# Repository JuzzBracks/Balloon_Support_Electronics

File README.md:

# Balloon_Support_Electronics
 Modular designs and support materials for scientific Ballooning support electronics. The goal is to lower the time/financial costs of developing and deploying scientific balloons.

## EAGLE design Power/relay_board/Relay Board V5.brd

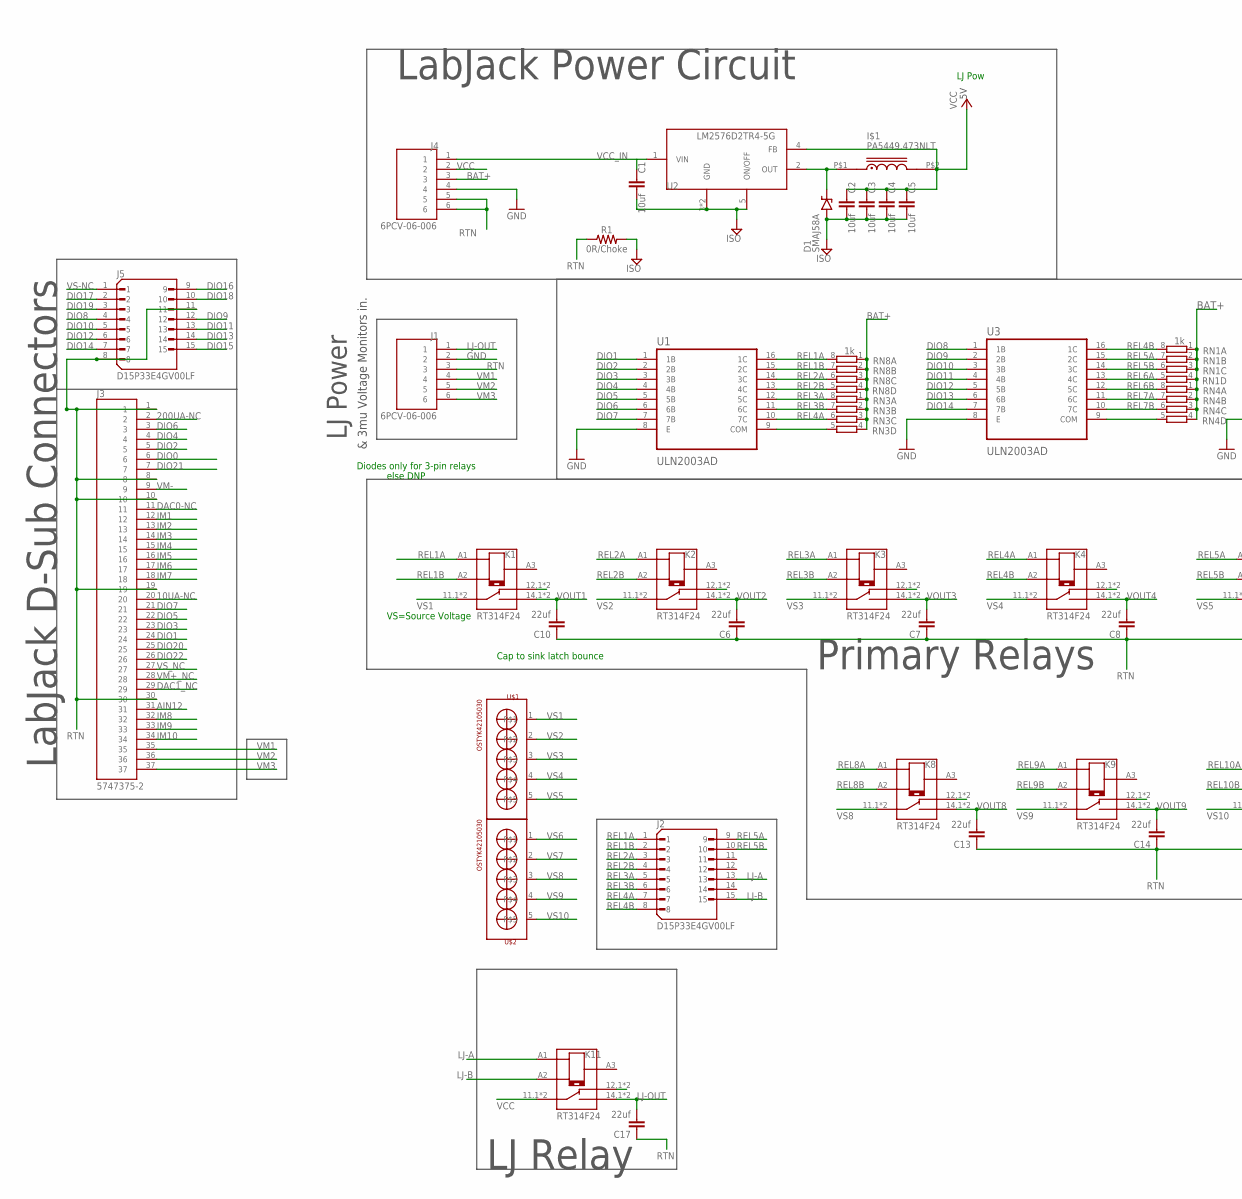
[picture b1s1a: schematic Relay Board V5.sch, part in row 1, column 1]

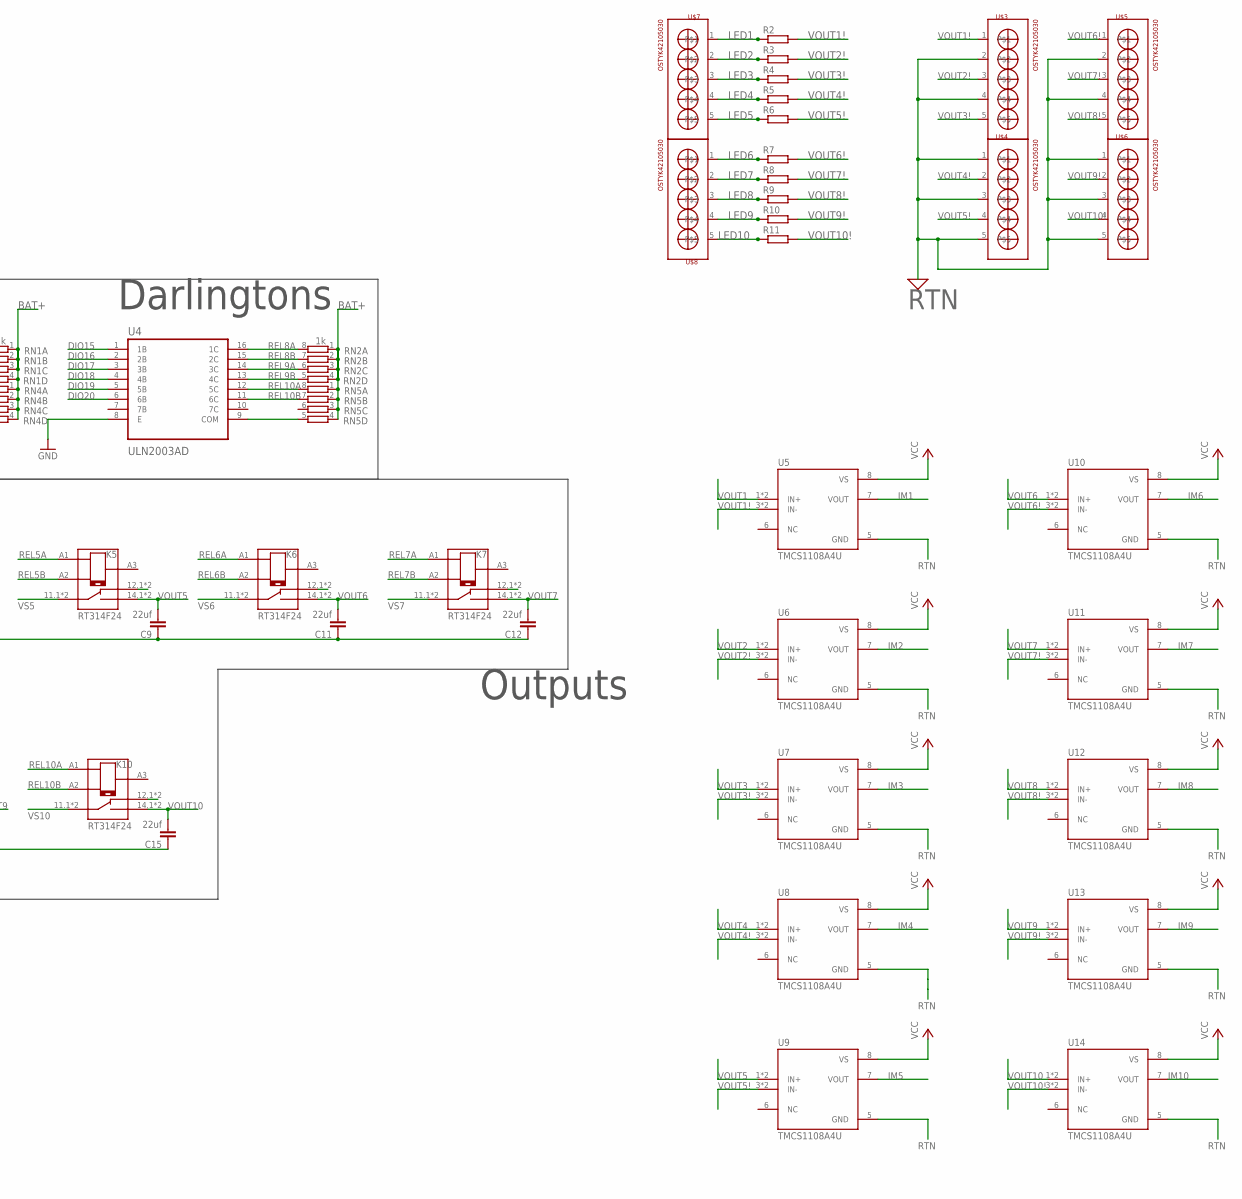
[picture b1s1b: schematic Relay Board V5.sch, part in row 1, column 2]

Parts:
C1, C2, C3, C4, C5: 10uf; 0805
C6, C7, C8, C9, C10, C11, C12, C13, C14, C15, C17: 22uf; 0603
D1: SMAJ58A; SMA
I$1: PA5449.473NLT; IND_TYS4020470M-10
J1, J4: 6PCV-06-006; TE_9-1437652-5
J2, J5: D15P33E4GV00LF; AMPHENOL_D15P33E4GV00LF
J3: 5747375-2; TE_5747375-2
K1, K2, K3, K4, K5, K6, K7, K8, K9, K10, K11: RT314F24; TE_8-1393239-8
R1: 0R/Choke; 0603
R2, R3, R4, R5, R6, R7, R8, R9, R10, R11: R-EU_0204/7; 0204/7
RN1, RN2, RN3, RN4, RN5, RN8: 1k; CAY16
U1, U3, U4: ULN2003AD; SOIC127P600X175-16N
U2: LM2576D2TR4-5G; D2PAK-5
U5, U6, U7, U8, U9, U10, U11, U12, U13, U14: TMCS1108A4U; SOIC127P599X175-8N
U$1, U$2, U$3, U$4, U$5, U$6, U$7, U$8: OSTYK42105030

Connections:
10UA-NC: J3.20
200UA-NC: J3.2
AGND: C1.2, C2.2, C3.2, C4.2, C5.2, D1.A, R1.2, U2.3 (GND), U2.5 (ON/OFF), U2.6 (GND)
AIN12: J3.31
BAT+: J4.3, RN1.1, RN1.2 (1), RN1.3 (1), RN1.4 (1), RN2.1, RN2.2 (1), RN2.3 (1), RN2.4 (1), RN3.1, RN3.2 (1), RN3.3 (1), RN3.4 (1), RN4.1, RN4.2 (1), RN4.3 (1), RN4.4 (1), RN5.1, RN5.2 (1), RN5.3 (1), RN5.4 (1), RN8.1, RN8.2 (1), RN8.3 (1), RN8.4 (1)
DAC0-NC: J3.11
DAC1_NC: J3.29
DIO0: J3.6
DIO1: J3.24, U1.1 (1B)
DIO2: J3.5, U1.2 (2B)
DIO3: J3.23, U1.3 (3B)
DIO4: J3.4, U1.4 (4B)
DIO5: J3.22, U1.5 (5B)
DIO6: J3.3, U1.6 (6B)
DIO7: J3.21, U1.7 (7B)
DIO8: J5.4, U3.1 (1B)
DIO9: J5.12, U3.2 (2B)
DIO10: J5.5, U3.3 (3B)
DIO11: J5.13, U3.4 (4B)
DIO12: J5.6, U3.5 (5B)
DIO13: J5.14, U3.6 (6B)
DIO14: J5.7, U3.7 (7B)
DIO15: J5.15, U4.1 (1B)
DIO16: J5.9, U4.2 (2B)
DIO17: J5.2, U4.3 (3B)
DIO18: J5.10, U4.4 (4B)
DIO19: J5.3, U4.5 (5B)
DIO20: J3.25, U4.6 (6B)
DIO21: J3.7
DIO22: J3.26
GND: J1.2, J4.4, U1.8 (E), U3.8 (E), U4.8 (E)
IM1: J3.12, U5.7 (VOUT)
IM2: J3.13, U6.7 (VOUT)
IM3: J3.14, U7.7 (VOUT)
IM4: J3.15, U8.7 (VOUT)
IM5: J3.16, U9.7 (VOUT)
IM6: J3.17, U10.7 (VOUT)
IM7: J3.18, U11.7 (VOUT)
IM8: J3.32, U12.7 (VOUT)
IM9: J3.33, U13.7 (VOUT)
IM10: J3.34, U14.7 (VOUT)
LED1: R2.1, U$7.1
LED2: R3.1, U$7.2
LED3: R4.1, U$7.3
LED4: R5.1, U$7.4
LED5: R6.1, U$7.5
LED6: R7.1, U$8.1
LED7: R8.1, U$8.2
LED8: R9.1, U$8.3
LED9: R10.1, U$8.4
LED10: R11.1, U$8.5
LJ-A: J2.13, K11.A1
LJ-B: J2.15, K11.A2
LJ-OUT: C17.2, J1.1, K11.14.1 (14), K11.14.2 (14)
unnamed: K1.12.1 (12), K1.12.2 (12)
unnamed: RN3.5 (2), U1.9 (COM)
unnamed: K2.12.1 (12), K2.12.2 (12)
unnamed: K3.12.1 (12), K3.12.2 (12)
unnamed: D1.C, I$1.P$1 (1), U2.2 (OUT)
unnamed: K4.12.1 (12), K4.12.2 (12)
unnamed: K5.12.1 (12), K5.12.2 (12)
unnamed: K6.12.1 (12), K6.12.2 (12)
unnamed: K7.12.1 (12), K7.12.2 (12)
unnamed: RN4.5 (2), U3.9 (COM)
unnamed: K8.12.1 (12), K8.12.2 (12)
unnamed: K9.12.1 (12), K9.12.2 (12)
unnamed: K10.12.1 (12), K10.12.2 (12)
unnamed: RN5.5 (2), U4.9 (COM)
unnamed: K11.12.1 (12), K11.12.2 (12)
REL1A: J2.1, K1.A1, RN8.8 (2), U1.16 (1C)
REL1B: J2.2, K1.A2, RN8.7 (2), U1.15 (2C)
REL2A: J2.3, K2.A1, RN8.6 (2), U1.14 (3C)
REL2B: J2.4, K2.A2, RN8.5 (2), U1.13 (4C)
REL3A: J2.5, K3.A1, RN3.8 (2), U1.12 (5C)
REL3B: J2.6, K3.A2, RN3.7 (2), U1.11 (6C)
REL4A: J2.7, K4.A1, RN3.6 (2), U1.10 (7C)
REL4B: J2.8, K4.A2, RN1.8 (2), U3.16 (1C)
REL5A: J2.9, K5.A1, RN1.7 (2), U3.15 (2C)
REL5B: J2.10, K5.A2, RN1.6 (2), U3.14 (3C)
REL6A: K6.A1, RN1.5 (2), U3.13 (4C)
REL6B: K6.A2, RN4.8 (2), U3.12 (5C)
REL7A: K7.A1, RN4.7 (2), U3.11 (6C)
REL7B: K7.A2, RN4.6 (2), U3.10 (7C)
REL8A: K8.A1, RN2.8 (2), U4.16 (1C)
REL8B: K8.A2, RN2.7 (2), U4.15 (2C)
REL9A: K9.A1, RN2.6 (2), U4.14 (3C)
REL9B: K9.A2, RN2.5 (2), U4.13 (4C)
REL10A: K10.A1, RN5.8 (2), U4.12 (5C)
REL10B: K10.A2, RN5.7 (2), U4.11 (6C)
RTN: C6.1, C7.1, C8.1, C9.1, C10.1, C11.1, C12.1, C13.1, C14.1, C15.1, C17.1, J1.3, J3.1, J3.8, J3.10, J3.19, J3.30, J4.5, J4.6, J5.8, J5.11, R1.1, U5.5 (GND), U6.5 (GND), U7.5 (GND), U8.5 (GND), U9.5 (GND), U10.5 (GND), U11.5 (GND), U12.5 (GND), U13.5 (GND), U14.5 (GND), U$3.2, U$3.4, U$4.1, U$4.3, U$4.5, U$5.2, U$5.4, U$6.1, U$6.3, U$6.5
VCC: C2.1, C3.1, C4.1, C5.1, I$1.P$2 (2), J4.2, K11.11.1 (11), K11.11.2 (11), U2.4 (FB), U5.8 (VS), U6.8 (VS), U7.8 (VS), U8.8 (VS), U9.8 (VS), U10.8 (VS), U11.8 (VS), U12.8 (VS), U13.8 (VS), U14.8 (VS)
VCC_IN: J4.1, U2.1 (VIN)
VM1: J1.4, J3.35
VM2: J1.5, J3.36
VM3: J1.6, J3.37
VM+_NC: J3.28
VM-: J3.9
VOUT1: C10.2, K1.14.1 (14), K1.14.2 (14), U5.1 (IN+), U5.2 (IN+)
VOUT1!: R2.2, U5.3 (IN-), U5.4 (IN-), U$3.1
VOUT2: C6.2, K2.14.1 (14), K2.14.2 (14), U6.1 (IN+), U6.2 (IN+)
VOUT2!: R3.2, U6.3 (IN-), U6.4 (IN-), U$3.3
VOUT3: C7.2, K3.14.1 (14), K3.14.2 (14), U7.1 (IN+), U7.2 (IN+)
VOUT3!: R4.2, U7.3 (IN-), U7.4 (IN-), U$3.5
VOUT4: C8.2, K4.14.1 (14), K4.14.2 (14), U8.1 (IN+), U8.2 (IN+)
VOUT4!: R5.2, U8.3 (IN-), U8.4 (IN-), U$4.2
VOUT5: C9.2, K5.14.1 (14), K5.14.2 (14), U9.1 (IN+), U9.2 (IN+)
VOUT5!: R6.2, U9.3 (IN-), U9.4 (IN-), U$4.4
VOUT6: C11.2, K6.14.1 (14), K6.14.2 (14), U10.1 (IN+), U10.2 (IN+)
VOUT6!: R7.2, U10.3 (IN-), U10.4 (IN-), U$5.1
VOUT7: C12.2, K7.14.1 (14), K7.14.2 (14), U11.1 (IN+), U11.2 (IN+)
VOUT7!: R8.2, U11.3 (IN-), U11.4 (IN-), U$5.3
VOUT8: C13.2, K8.14.1 (14), K8.14.2 (14), U12.1 (IN+), U12.2 (IN+)
VOUT8!: R9.2, U12.3 (IN-), U12.4 (IN-), U$5.5
VOUT9: C14.2, K9.14.1 (14), K9.14.2 (14), U13.1 (IN+), U13.2 (IN+)
VOUT9!: R10.2, U13.3 (IN-), U13.4 (IN-), U$6.2
VOUT10: C15.2, K10.14.1 (14), K10.14.2 (14), U14.1 (IN+), U14.2 (IN+)
VOUT10!: R11.2, U14.3 (IN-), U14.4 (IN-), U$6.4
VS1: K1.11.1 (11), K1.11.2 (11), U$1.1
VS2: K2.11.1 (11), K2.11.2 (11), U$1.2
VS3: K3.11.1 (11), K3.11.2 (11), U$1.3
VS4: K4.11.1 (11), K4.11.2 (11), U$1.4
VS5: K5.11.1 (11), K5.11.2 (11), U$1.5
VS6: K6.11.1 (11), K6.11.2 (11), U$2.1
VS7: K7.11.1 (11), K7.11.2 (11), U$2.2
VS8: K8.11.1 (11), K8.11.2 (11), U$2.3
VS9: K9.11.1 (11), K9.11.2 (11), U$2.4
VS10: K10.11.1 (11), K10.11.2 (11), U$2.5
VS-NC: J5.1
VS_NC: J3.27

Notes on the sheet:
VS=Source Voltage
Diodes only for 3-pin relays
else DNP
Cap to sink latch bounce
LJ Pow
LabJack Power Circuit
Darlingtons
Primary Relays
LJ Relay
Outputs
LabJack D-Sub Connectors
LJ Power
& 3mu Voltage Monitors in.

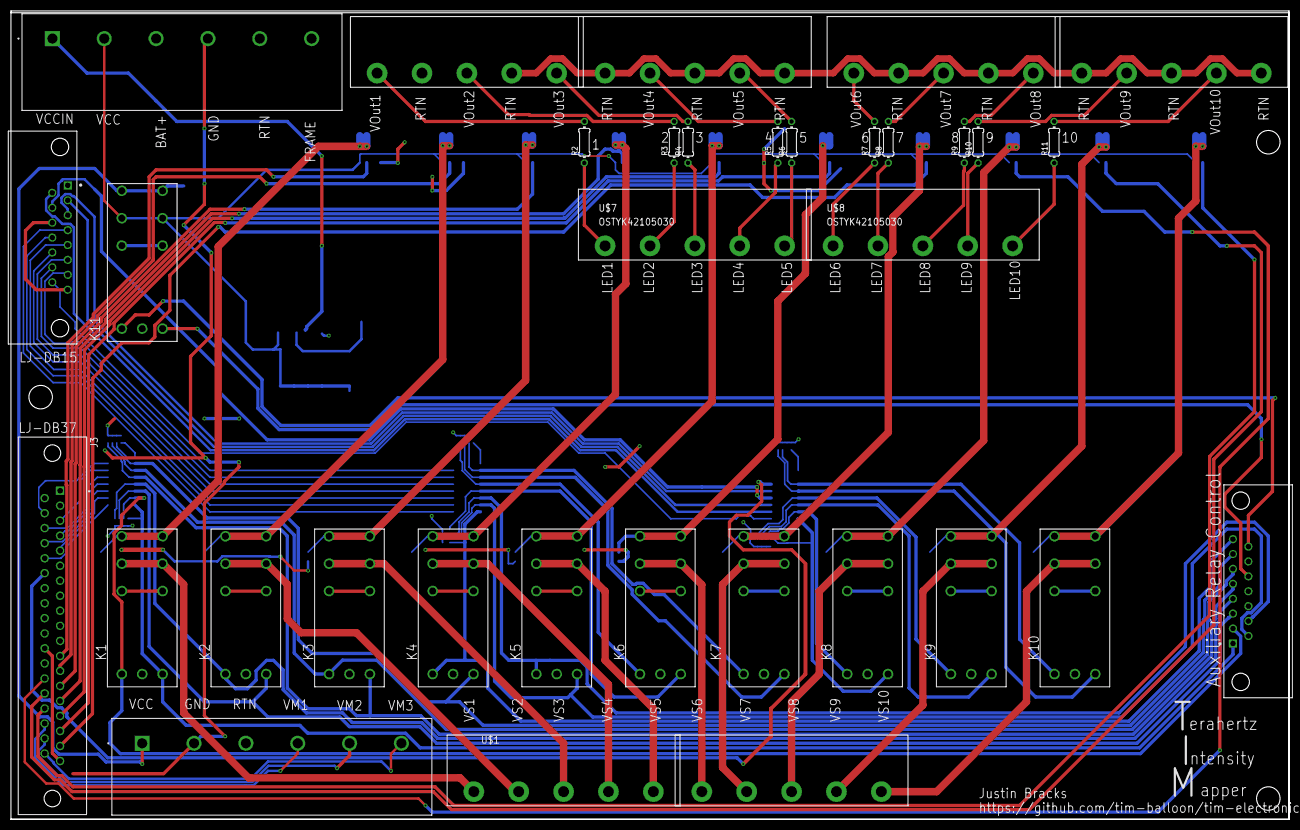
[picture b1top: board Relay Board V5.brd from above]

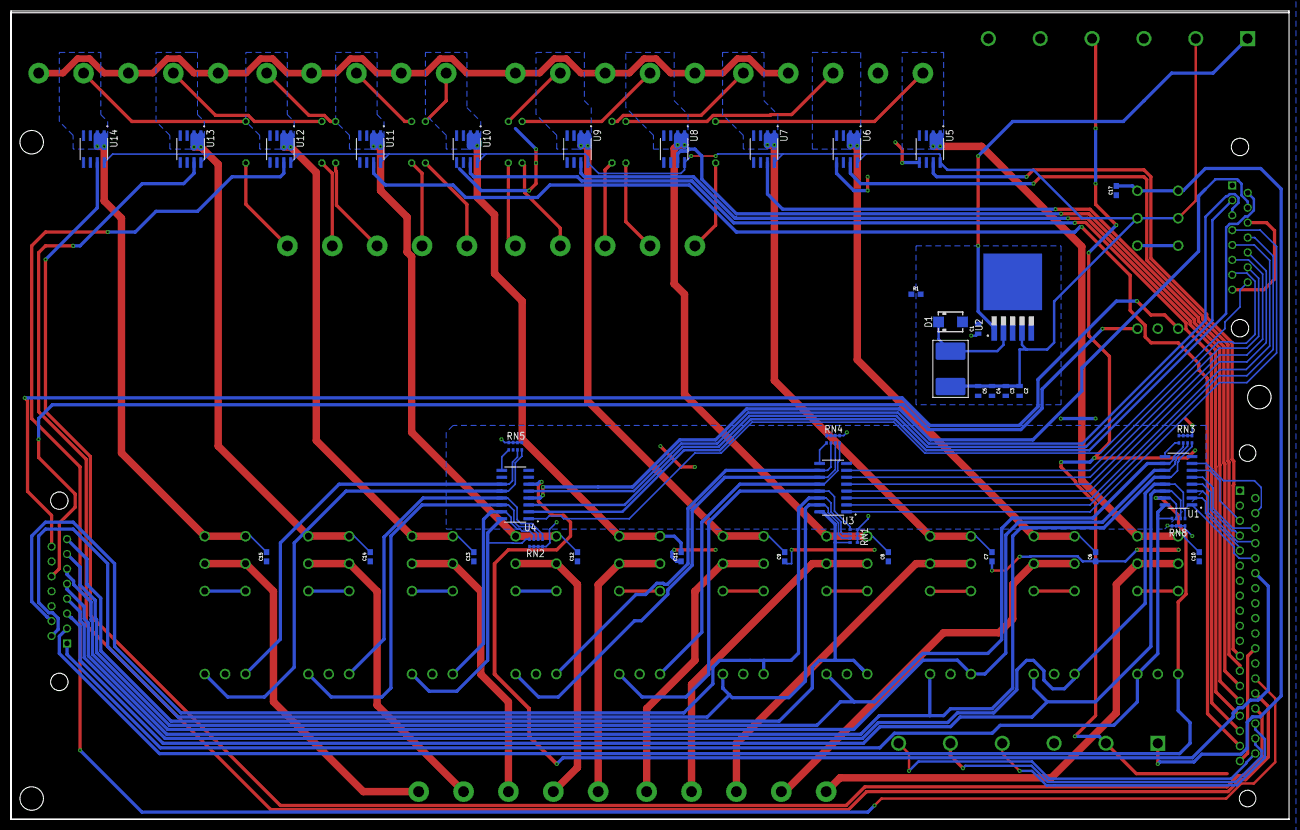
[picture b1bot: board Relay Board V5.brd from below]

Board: 2 copper layers, 234.9 x 148.6 mm, 73 parts (39 on the bottom side), 117 nets.

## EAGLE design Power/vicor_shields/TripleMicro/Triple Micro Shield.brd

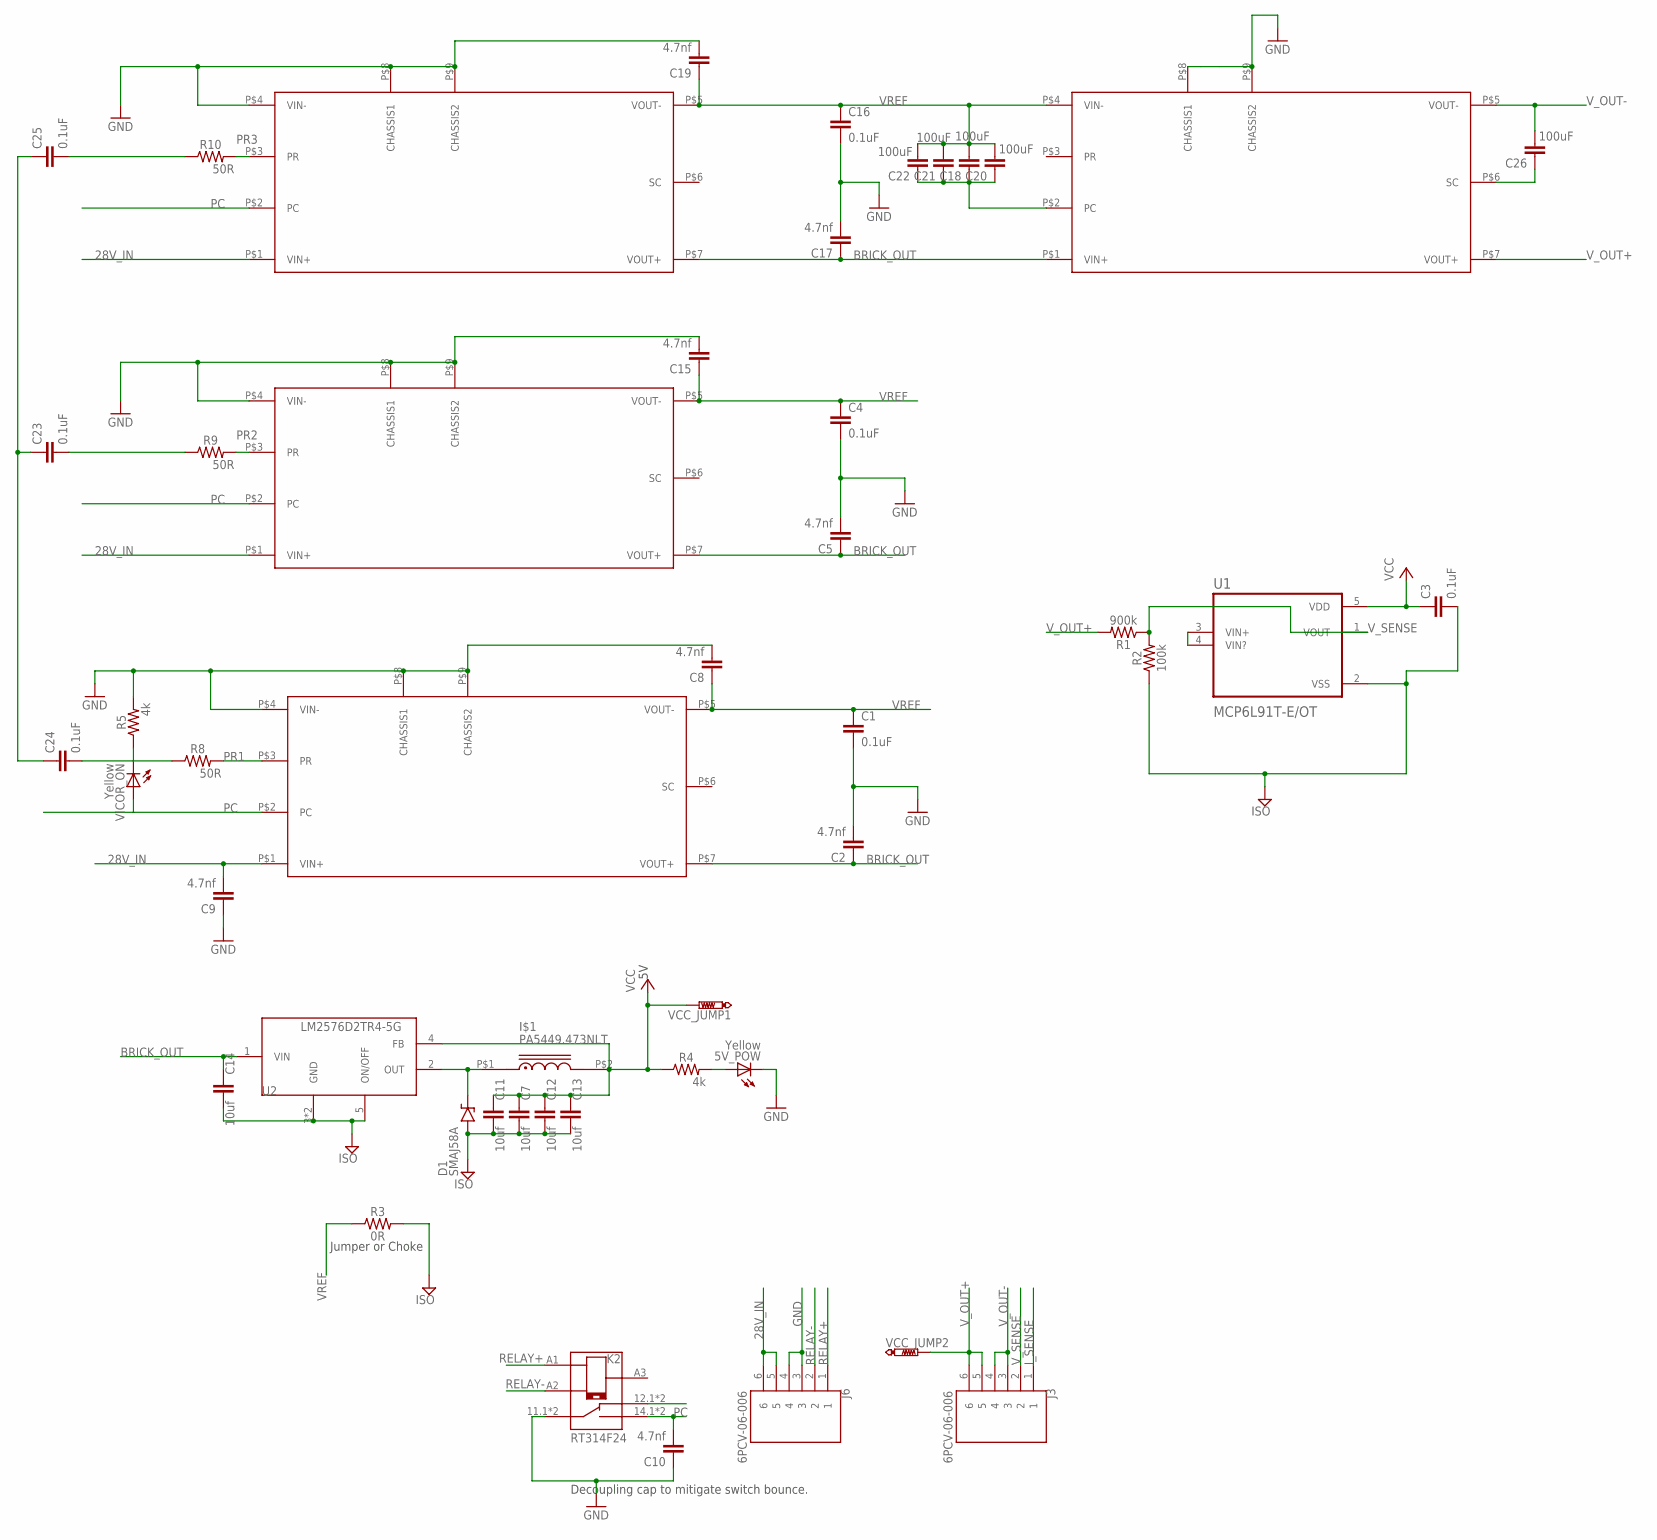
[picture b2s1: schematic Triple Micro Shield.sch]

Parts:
5V_POW: Yellow; CHIPLED_0805
C1, C3, C4, C16, C23, C24, C25: 0.1uF; 0603
C2, C5, C8, C9, C10, C15, C17, C19: 4.7nf; 0603
C7, C11, C12, C13, C14: 10uf; 0805
C18, C20, C21, C22, C26: 100uF; 0603
D1: SMAJ58A; SMA
I$1: PA5449.473NLT; IND_TYS4020470M-10
J3, J6: 6PCV-06-006; TE_9-1437652-5
K2: RT314F24; TE_8-1393239-8
R1: 900k; 0603
R2: 100k; 0603
R3: 0R; 0603
R4, R5: 4k; 0603
R8, R9, R10: 50R; 0603
U1: MCP6L91T-E/OT; SOT95P270X145-5N
U2: LM2576D2TR4-5G; D2PAK-5
U$2, U$3, U$4, U$5: VICOR_MINI_BRICK_VICORMINIBRICK; VICOR_MINI_BRICK_MINIBRICK
VCC_JUMP1, VCC_JUMP2: PTR1PAD1-13; P1-13
VICOR_ON: Yellow; CHIPLED_0805

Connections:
28V_IN: C9.2, J6.5, J6.6, U$2.P$1 (VIN+), U$3.P$1 (VIN+), U$4.P$1 (VIN+)
AGND: C3.2, C7.2, C11.2, C12.2, C13.2, C14.2, D1.A, R2.1, R3.2, U1.2 (VSS), U2.3 (GND), U2.5 (ON/OFF), U2.6 (GND)
BRICK_OUT: C2.1, C5.1, C14.1, C17.1, U2.1 (VIN), U$2.P$7 (VOUT+), U$3.P$7 (VOUT+), U$4.P$7 (VOUT+), U$5.P$1 (VIN+)
GND: 5V_POW.C, C1.2, C2.2, C4.2, C5.2, C8.2, C9.1, C10.1, C15.2, C16.2, C17.2, C19.2, J6.3, J6.4, K2.11.1 (11), K2.11.2 (11), R5.2, U$2.P$4 (VIN-), U$2.P$8 (CHASSIS1), U$2.P$9 (CHASSIS2), U$3.P$4 (VIN-), U$3.P$8 (CHASSIS1), U$3.P$9 (CHASSIS2), U$4.P$4 (VIN-), U$4.P$8 (CHASSIS1), U$4.P$9 (CHASSIS2), U$5.P$8 (CHASSIS1), U$5.P$9 (CHASSIS2)
IN+: R1.1, R2.2, U1.1 (VOUT)
I_SENSE: J3.1
unnamed: K2.12.1 (12), K2.12.2 (12)
unnamed: 5V_POW.A, R4.2
unnamed: R5.1, VICOR_ON.C
unnamed: C18.1, C20.1, C21.1, C22.1, U$5.P$2 (PC)
unnamed: D1.C, I$1.P$1 (1), U2.2 (OUT)
unnamed: C23.2, R9.1
unnamed: C23.1, C24.1, C25.1
unnamed: C24.2, R8.1
unnamed: C25.2, R10.1
unnamed: C26.1, U$5.P$6 (SC)
PC: C10.2, K2.14.1 (14), K2.14.2 (14), U$2.P$2 (PC), U$3.P$2 (PC), U$4.P$2 (PC), VICOR_ON.A
PR1: R8.2, U$2.P$3 (PR)
PR2: R9.2, U$3.P$3 (PR)
PR3: R10.2, U$4.P$3 (PR)
RELAY+: J6.1, K2.A1
RELAY-: J6.2, K2.A2
VCC: C3.1, C7.1, C11.1, C12.1, C13.1, I$1.P$2 (2), R4.1, U1.5 (VDD), U2.4 (FB), VCC_JUMP1.TP
VREF: C1.1, C4.1, C8.1, C15.1, C16.1, C18.2, C19.1, C20.2, C21.2, C22.2, R3.1, U$2.P$5 (VOUT-), U$3.P$5 (VOUT-), U$4.P$5 (VOUT-), U$5.P$4 (VIN-)
V_OUT+: J3.5, J3.6, R1.2, U$5.P$7 (VOUT+), VCC_JUMP2.TP
V_OUT-: C26.2, J3.3, J3.4, U$5.P$5 (VOUT-)
V_SENSE: J3.2, U1.3 (VIN+), U1.4 (VIN?)

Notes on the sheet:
Decoupling cap to mitigate switch bounce.
Jumper or Choke

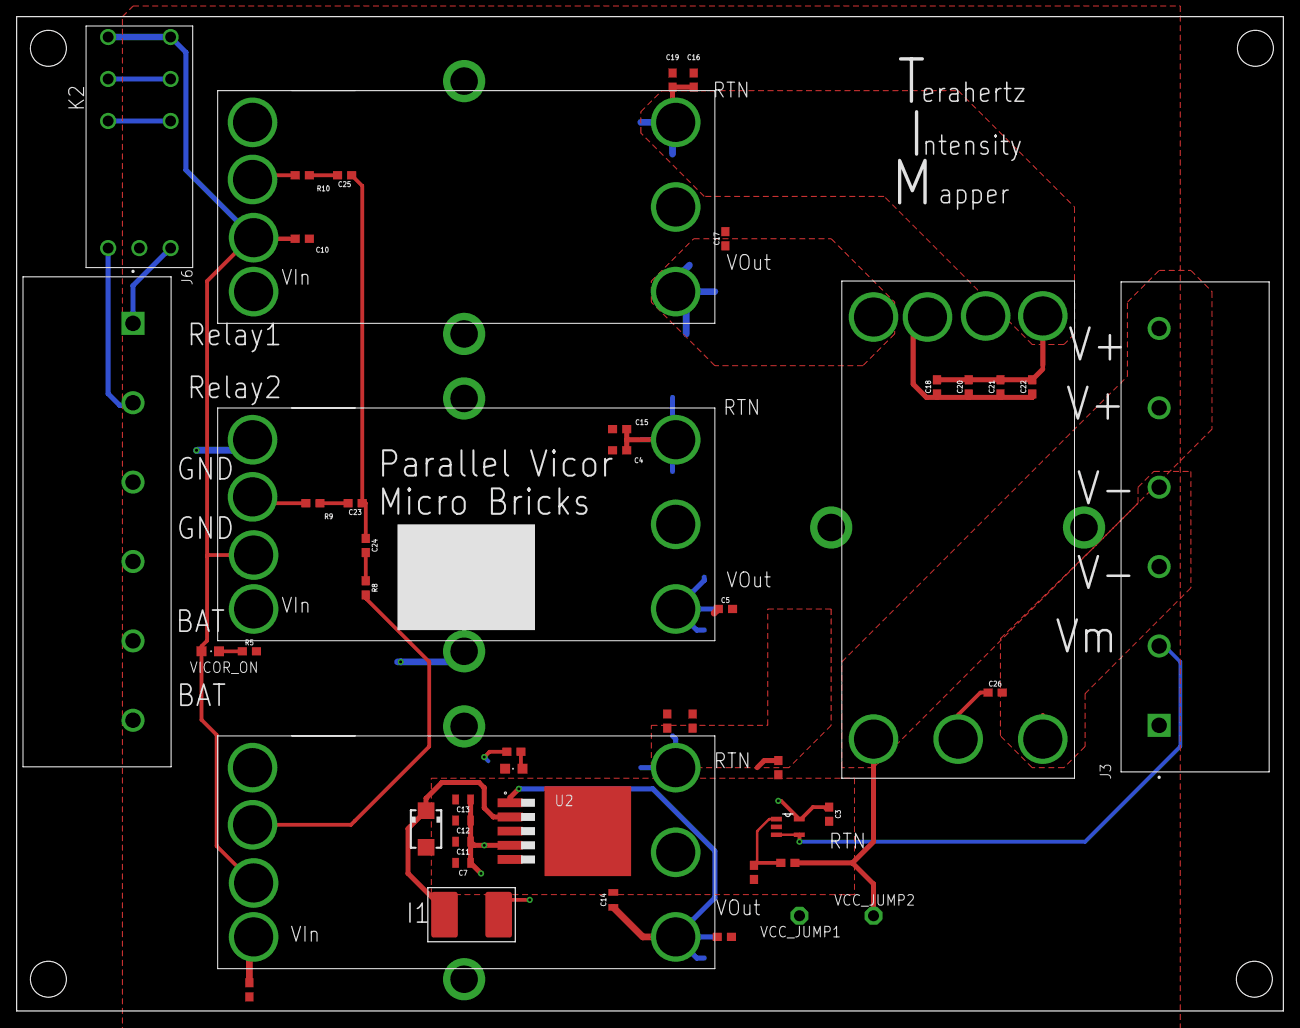
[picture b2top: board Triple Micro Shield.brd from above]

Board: 2 copper layers, 152.1 x 119.4 mm, 48 parts (0 on the bottom side), 26 nets.

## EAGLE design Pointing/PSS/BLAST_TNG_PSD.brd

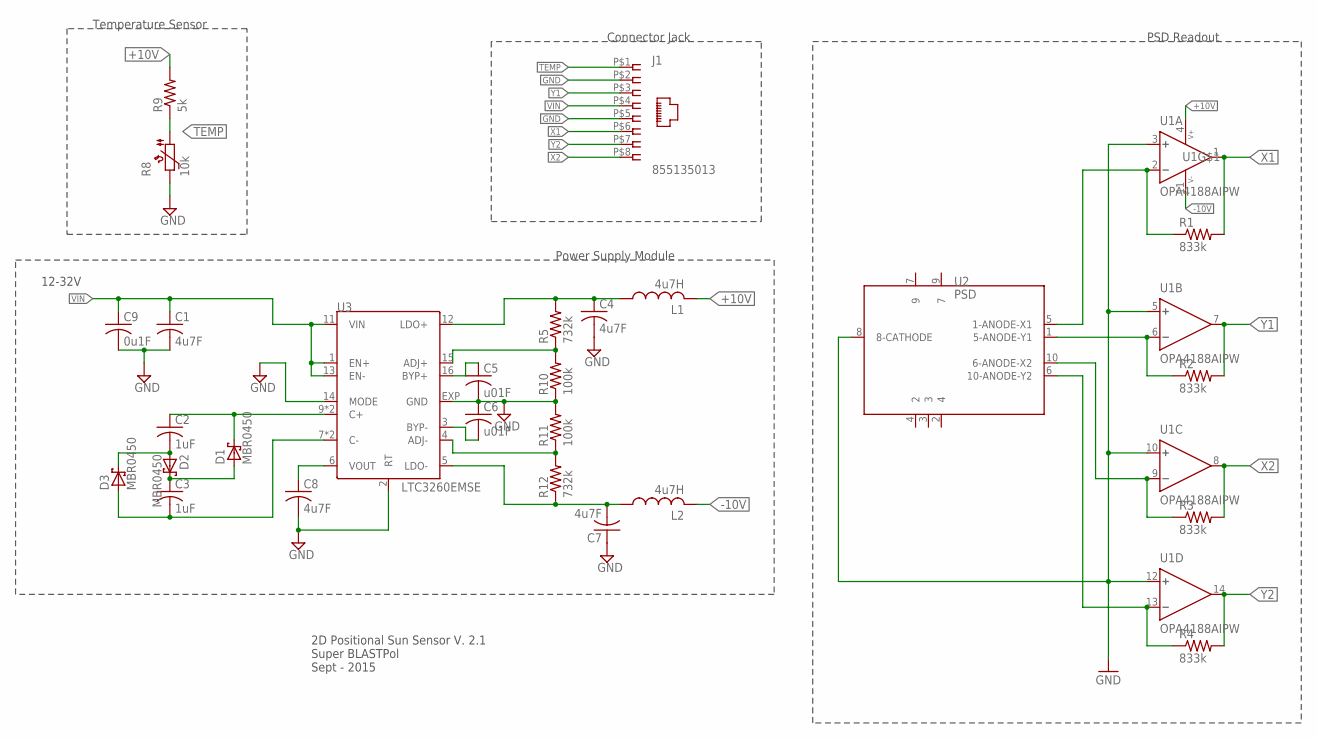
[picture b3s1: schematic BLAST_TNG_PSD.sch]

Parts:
C1, C4, C7, C8: 4u7F; C1210; MPN CL31A475KOHNNNE
C2, C3: 1uF; C1206
C5, C6: u01F; C0805
C9: 0u1F; C0805
D1, D2, D3: MBR0450; SOD123
J1: 855135013; MPN 85513-5013
L1, L2: 4u7H; L2012C
R1, R2, R3, R4: 833k; M0805
R5, R12: 732k; R0805
R8: 10k; L3216C; MPN KPTL-3216CGCK
R9: 5k; R0805
R10, R11: 100k; R0805
U1: OPA4188AIPW; TSSOP14
U2: PSD; PSD-S5991
U3: LTC3260EMSE; MSOP16

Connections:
+10V: L1.2, R9.2, U1.4 (V+)
-10V: L2.2, U1.11 (V-)
D1X1: R1.1, U1.2 (-), U2.5 (1-ANODE-X1)
D1X2: R3.1, U1.9 (-), U2.10 (6-ANODE-X2)
D1Y1: R2.1, U1.6 (-), U2.1 (5-ANODE-Y1)
D1Y2: R4.1, U1.13 (-), U2.6 (10-ANODE-Y2)
FLY+: C2.1, D1.C, U3.9 (C+), U3.10 (C+)
FLY-: C3.2, D3.A, U3.7 (C-), U3.8 (C-)
GND: C1.2, C4.2, C5.2, C6.1, C7.1, C8.2, C9.2, J1.P$2 (2), J1.P$5 (5), R8.2, R10.1, R11.2, U1.3 (+), U1.5 (+), U1.10 (+), U1.12 (+), U2.8 (8-CATHODE), U3.2 (RT), U3.14 (MODE), U3.EXP (GND)
LDO+: C4.1, L1.1, R5.2, U3.12 (LDO+)
LDO-: C7.2, L2.1, R12.1, U3.5 (LDO-)
unnamed: C8.1, U3.6 (VOUT)
unnamed: C3.1, D1.A, D2.C
unnamed: C2.2, D2.A, D3.C
unnamed: C6.2, U3.3 (BYP-)
unnamed: C5.1, U3.16 (BYP+)
unnamed: R5.1, R10.2, U3.15 (ADJ+)
unnamed: R11.1, R12.2, U3.4 (ADJ-)
TEMP: J1.P$1 (1), R8.1, R9.1
VIN: C1.1, C9.1, J1.P$4 (4), U3.1 (EN+), U3.11 (VIN), U3.13 (EN-)
X1: J1.P$6 (6), R1.2, U1.1 (OUT)
X2: J1.P$8 (8), R3.2, U1.8 (OUT)
Y1: J1.P$3 (3), R2.2, U1.7 (OUT)
Y2: J1.P$7 (7), R4.2, U1.14 (OUT)

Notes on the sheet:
Power Supply Module
12-32V
Connector Jack
Temperature Sensor
PSD Readout
2D Positional Sun Sensor V. 2.1 Super BLASTPol Sept - 2015

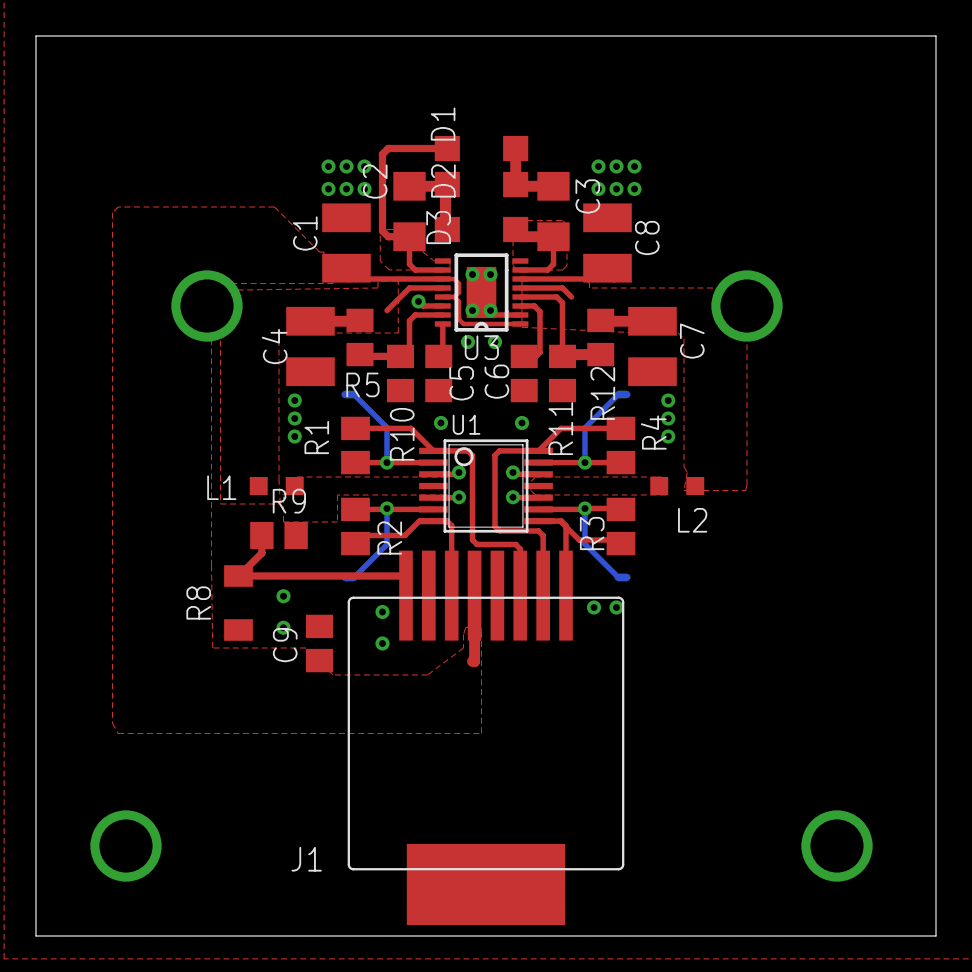
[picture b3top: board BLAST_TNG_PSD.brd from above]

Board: 2 copper layers, 50.0 x 50.0 mm, 28 parts (1 on the bottom side), 24 nets.

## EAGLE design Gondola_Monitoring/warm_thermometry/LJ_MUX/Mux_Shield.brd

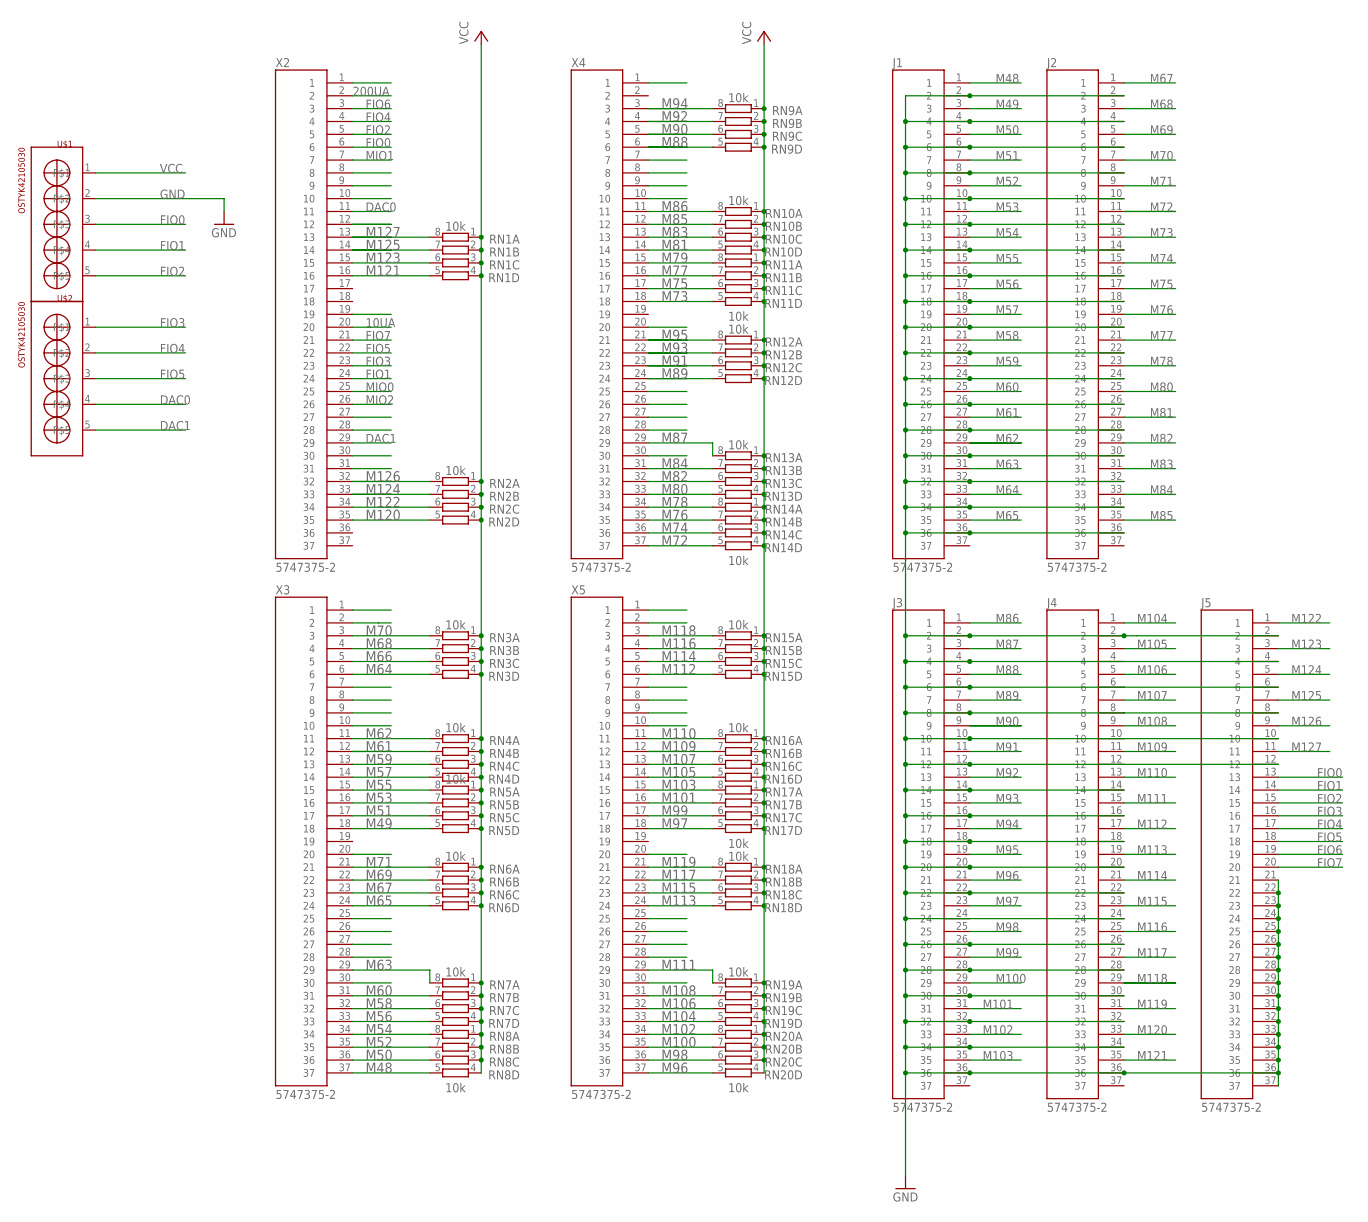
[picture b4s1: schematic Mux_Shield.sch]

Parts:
J1, J2, J3, J4, J5: 5747375-2; TE_5747375-2
RN1, RN2, RN3, RN4, RN5, RN6, RN7, RN8, RN9, RN10, RN11, RN12, RN13, RN14, RN15, RN16, RN17, RN18, RN19, RN20: 10k; CAY16
U$1, U$2: OSTYK42105030
X2, X3, X4, X5: 5747375-2; TE_5747375-2

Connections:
10UA: X2.20
200UA: X2.2
DAC0: U$2.4, X2.11
DAC1: U$2.5, X2.29
FIO0: J5.13, U$1.3, X2.6
FIO1: J5.14, U$1.4, X2.24
FIO2: J5.15, U$1.5, X2.5
FIO3: J5.16, U$2.1, X2.23
FIO4: J5.17, U$2.2, X2.4
FIO5: J5.18, U$2.3, X2.22
FIO6: J5.19, X2.3
FIO7: J5.20, X2.21
GND: J1.2, J1.4, J1.6, J1.8, J1.10, J1.12, J1.14, J1.16, J1.18, J1.20, J1.22, J1.24, J1.26, J1.28, J1.30, J1.32, J1.34, J1.36, J2.2, J2.4, J2.6, J2.8, J2.10, J2.12, J2.14, J2.16, J2.18, J2.20, J2.22, J2.24, J2.26, J2.28, J2.30, J2.32, J2.34, J2.36, J3.2, J3.4, J3.6, J3.8, J3.10, J3.12, J3.14, J3.16, J3.18, J3.20, J3.22, J3.24, J3.26, J3.28, J3.30, J3.32, J3.34, J3.36, J4.2, J4.4, J4.6, J4.8, J4.10, J4.12, J4.14, J4.16, J4.18, J4.20, J4.22, J4.24, J4.26, J4.28, J4.30, J4.32, J4.34, J4.36, J5.2, J5.4, J5.6, J5.8, J5.10, J5.12, J5.21, J5.22, J5.23, J5.24, J5.25, J5.26, J5.27, J5.28, J5.29, J5.30, J5.31, J5.32, J5.33, J5.34, J5.35, J5.36, J5.37, U$1.2
M48: J1.1, RN8.5 (2), X3.37
M49: J1.3, RN5.5 (2), X3.18
M50: J1.5, RN8.6 (2), X3.36
M51: J1.7, RN5.6 (2), X3.17
M52: J1.9, RN8.7 (2), X3.35
M53: J1.11, RN5.7 (2), X3.16
M54: J1.13, RN8.8 (2), X3.34
M55: J1.15, RN5.8 (2), X3.15
M56: J1.17, RN7.5 (2), X3.33
M57: J1.19, RN4.5 (2), X3.14
M58: J1.21, RN7.6 (2), X3.32
M59: J1.23, RN4.6 (2), X3.13
M60: J1.25, RN7.7 (2), X3.31
M61: J1.27, RN4.7 (2), X3.12
M62: RN4.8 (2), X3.11
M63: J1.31, RN7.8 (2), X3.29
M64: J1.33, RN3.5 (2), X3.6
M65: J1.35, RN6.5 (2), X3.24
M66: RN3.6 (2), X3.5
M67: J2.1, RN6.6 (2), X3.23
M68: J2.3, RN3.7 (2), X3.4
M69: J2.5, RN6.7 (2), X3.22
M70: J2.7, RN3.8 (2), X3.3
M71: J2.9, RN6.8 (2), X3.21
M72: J2.11, RN14.5 (2), X4.37
M73: J2.13, RN11.5 (2), X4.18
M74: J2.15, RN14.6 (2), X4.36
M75: J2.17, RN11.6 (2), X4.17
M76: J2.19, RN14.7 (2), X4.35
M77: J2.21, RN11.7 (2), X4.16
M78: J2.23, RN14.8 (2), X4.34
M79: RN11.8 (2), X4.15
M80: J2.25, RN13.5 (2), X4.33
M81: J2.27, RN10.5 (2), X4.14
M82: J2.29, RN13.6 (2), X4.32
M83: J2.31, RN10.6 (2), X4.13
M84: J2.33, RN13.7 (2), X4.31
M85: J2.35, RN10.7 (2), X4.12
M86: J3.1, RN10.8 (2), X4.11
M87: J3.3, RN13.8 (2), X4.29
M88: J3.5, RN9.5 (2), X4.6
M89: J3.7, RN12.5 (2), X4.24
M90: RN9.6 (2), X4.5
M91: J3.11, RN12.6 (2), X4.23
M92: J3.13, RN9.7 (2), X4.4
M93: J3.15, RN12.7 (2), X4.22
M94: J3.17, RN9.8 (2), X4.3
M95: J3.19, RN12.8 (2), X4.21
M96: J3.21, RN20.5 (2), X5.37
M97: J3.23, RN17.5 (2), X5.18
M98: J3.25, RN20.6 (2), X5.36
M99: J3.27, RN17.6 (2), X5.17
M100: J3.29, RN20.7 (2), X5.35
M101: J3.31, RN17.7 (2), X5.16
M102: J3.33, RN20.8 (2), X5.34
M103: J3.35, RN17.8 (2), X5.15
M104: J4.1, RN19.5 (2), X5.33
M105: J4.3, RN16.5 (2), X5.14
M106: J4.5, RN19.6 (2), X5.32
M107: J4.7, RN16.6 (2), X5.13
M108: J4.9, RN19.7 (2), X5.31
M109: J4.11, RN16.7 (2), X5.12
M110: J4.13, RN16.8 (2), X5.11
M111: J4.15, RN19.8 (2), X5.29
M112: J4.17, RN15.5 (2), X5.6
M113: J4.19, RN18.5 (2), X5.24
M114: J4.21, RN15.6 (2), X5.5
M115: J4.23, RN18.6 (2), X5.23
M116: J4.25, RN15.7 (2), X5.4
M117: J4.27, RN18.7 (2), X5.22
M118: RN15.8 (2), X5.3
M119: J4.31, RN18.8 (2), X5.21
M120: J4.33, RN2.5 (2), X2.35
M121: J4.35, RN1.5 (2), X2.16
M122: J5.1, RN2.6 (2), X2.34
M123: J5.3, RN1.6 (2), X2.15
M124: J5.5, RN2.7 (2), X2.33
M125: J5.7, RN1.7 (2), X2.14
M126: J5.9, RN2.8 (2), X2.32
M127: J5.11, RN1.8 (2), X2.13
MIO0: X2.25
MIO1: X2.7
MIO2: X2.26
VCC: RN1.1, RN1.2 (1), RN1.3 (1), RN1.4 (1), RN2.1, RN2.2 (1), RN2.3 (1), RN2.4 (1), RN3.1, RN3.2 (1), RN3.3 (1), RN3.4 (1), RN4.1, RN4.2 (1), RN4.3 (1), RN4.4 (1), RN5.1, RN5.2 (1), RN5.3 (1), RN5.4 (1), RN6.1, RN6.2 (1), RN6.3 (1), RN6.4 (1), RN7.1, RN7.2 (1), RN7.3 (1), RN7.4 (1), RN8.1, RN8.2 (1), RN8.3 (1), RN8.4 (1), RN9.1, RN9.2 (1), RN9.3 (1), RN9.4 (1), RN10.1, RN10.2 (1), RN10.3 (1), RN10.4 (1), RN11.1, RN11.2 (1), RN11.3 (1), RN11.4 (1), RN12.1, RN12.2 (1), RN12.3 (1), RN12.4 (1), RN13.1, RN13.2 (1), RN13.3 (1), RN13.4 (1), RN14.1, RN14.2 (1), RN14.3 (1), RN14.4 (1), RN15.1, RN15.2 (1), RN15.3 (1), RN15.4 (1), RN16.1, RN16.2 (1), RN16.3 (1), RN16.4 (1), RN17.1, RN17.2 (1), RN17.3 (1), RN17.4 (1), RN18.1, RN18.2 (1), RN18.3 (1), RN18.4 (1), RN19.1, RN19.2 (1), RN19.3 (1), RN19.4 (1), RN20.1, RN20.2 (1), RN20.3 (1), RN20.4 (1), U$1.1

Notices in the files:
parts and their libraries:
SparkFun-Capacitors: Licensing: Creative Commons ShareAlike 4.0 International - https://creativecommons.org/licenses/by-sa/4.0
